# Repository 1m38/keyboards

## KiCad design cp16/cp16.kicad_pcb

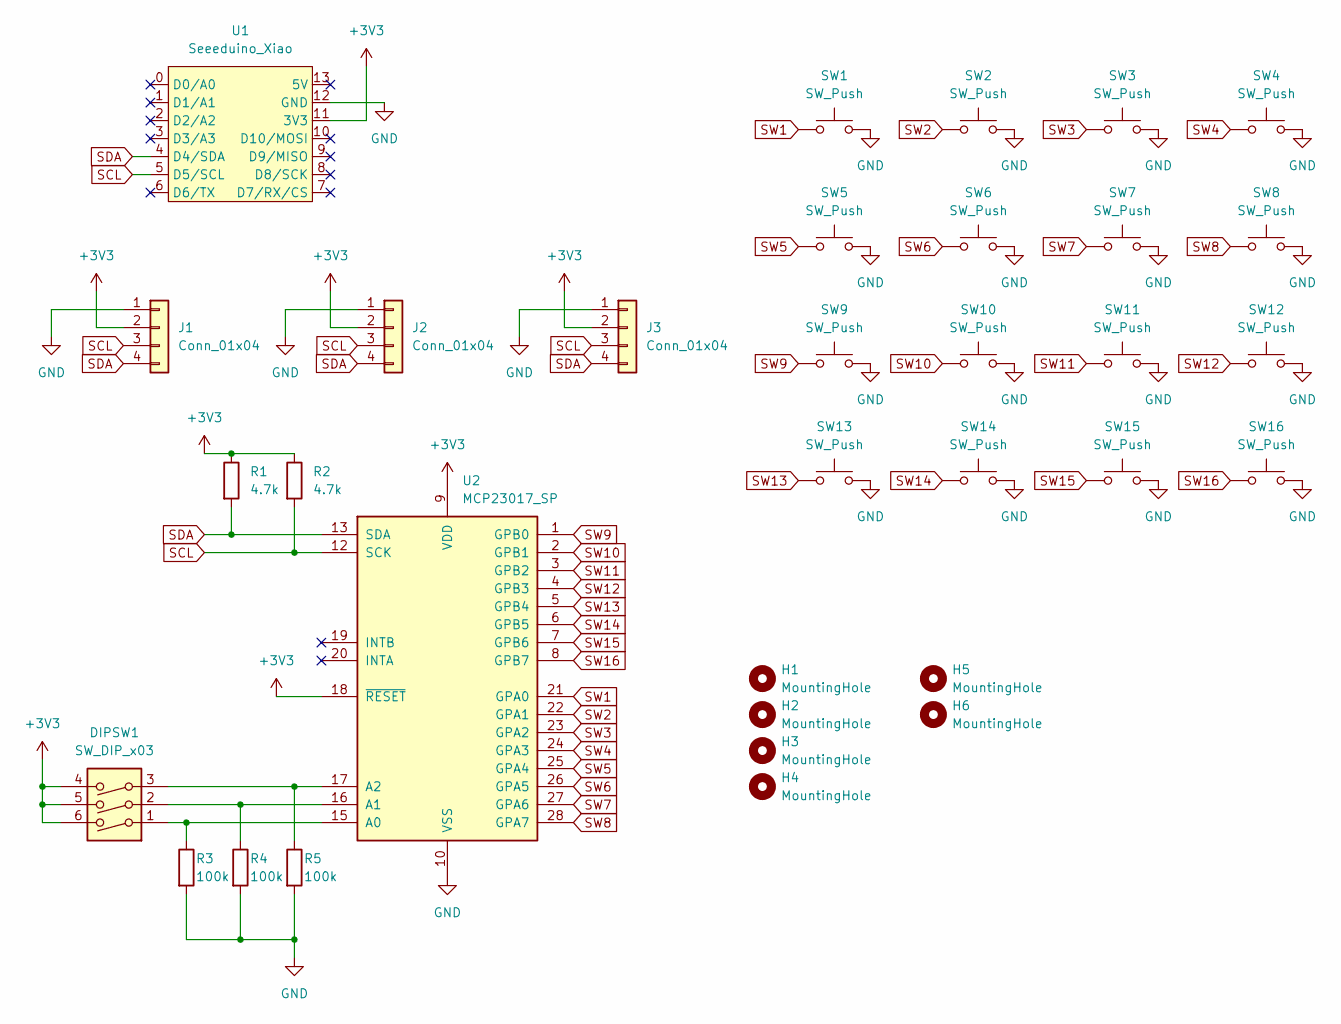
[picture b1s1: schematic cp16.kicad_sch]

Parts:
DIPSW1: SW_DIP_x03; DIP-6_W7.62mm
H1, H2, H3, H4: MountingHole; M2_HOLE_v2
H5, H6: MountingHole; M2_ScrewHole
J1, J2, J3: Conn_01x04; PinHeader_P2.54mm_I2C
R1, R2: 4.7k; R_Axial_DIN0207_L6.3mm_D2.5mm_P10.16mm_Horizontal
R3, R4, R5: 100k; R_Axial_DIN0207_L6.3mm_D2.5mm_P10.16mm_Horizontal
SW1, SW2, SW3, SW4, SW5, SW6, SW7, SW8, SW9, SW10, SW11, SW12, SW13, SW14, SW15, SW16: SW_Push; CherryMX_MidHeight_Choc_Hotswap_mod
U1: Seeeduino_Xiao; Seeed XIAO RP2040
U2: MCP23017_SP; DIP-28_W7.62mm

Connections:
+3V3: DIPSW1.4, DIPSW1.5, DIPSW1.6, J1.2, J2.2, J3.2, R1.1, R2.1, U1.11 (3V3), U2.9 (VDD), U2.18 (~RESET)
GND: J1.1, J2.1, J3.1, R3.2, R4.2, R5.2, SW1.2, SW2.2, SW3.2, SW4.2, SW5.2, SW6.2, SW7.2, SW8.2, SW9.2, SW10.2, SW11.2, SW12.2, SW13.2, SW14.2, SW15.2, SW16.2, U1.12 (GND), U2.10 (VSS)
unnamed: DIPSW1.1, R3.1, U2.15 (A0)
unnamed: DIPSW1.2, R4.1, U2.16 (A1)
unnamed: DIPSW1.3, R5.1, U2.17 (A2)
SCL: J1.3, J2.3, J3.3, R2.2, U1.5 (D5/SCL), U2.12 (SCK)
SDA: J1.4, J2.4, J3.4, R1.2, U1.4 (D4/SDA), U2.13 (SDA)
SW1: SW1.1, U2.21 (GPA0)
SW2: SW2.1, U2.22 (GPA1)
SW3: SW3.1, U2.23 (GPA2)
SW4: SW4.1, U2.24 (GPA3)
SW5: SW5.1, U2.25 (GPA4)
SW6: SW6.1, U2.26 (GPA5)
SW7: SW7.1, U2.27 (GPA6)
SW8: SW8.1, U2.28 (GPA7)
SW9: SW9.1, U2.1 (GPB0)
SW10: SW10.1, U2.2 (GPB1)
SW11: SW11.1, U2.3 (GPB2)
SW12: SW12.1, U2.4 (GPB3)
SW13: SW13.1, U2.5 (GPB4)
SW14: SW14.1, U2.6 (GPB5)
SW15: SW15.1, U2.7 (GPB6)
SW16: SW16.1, U2.8 (GPB7)

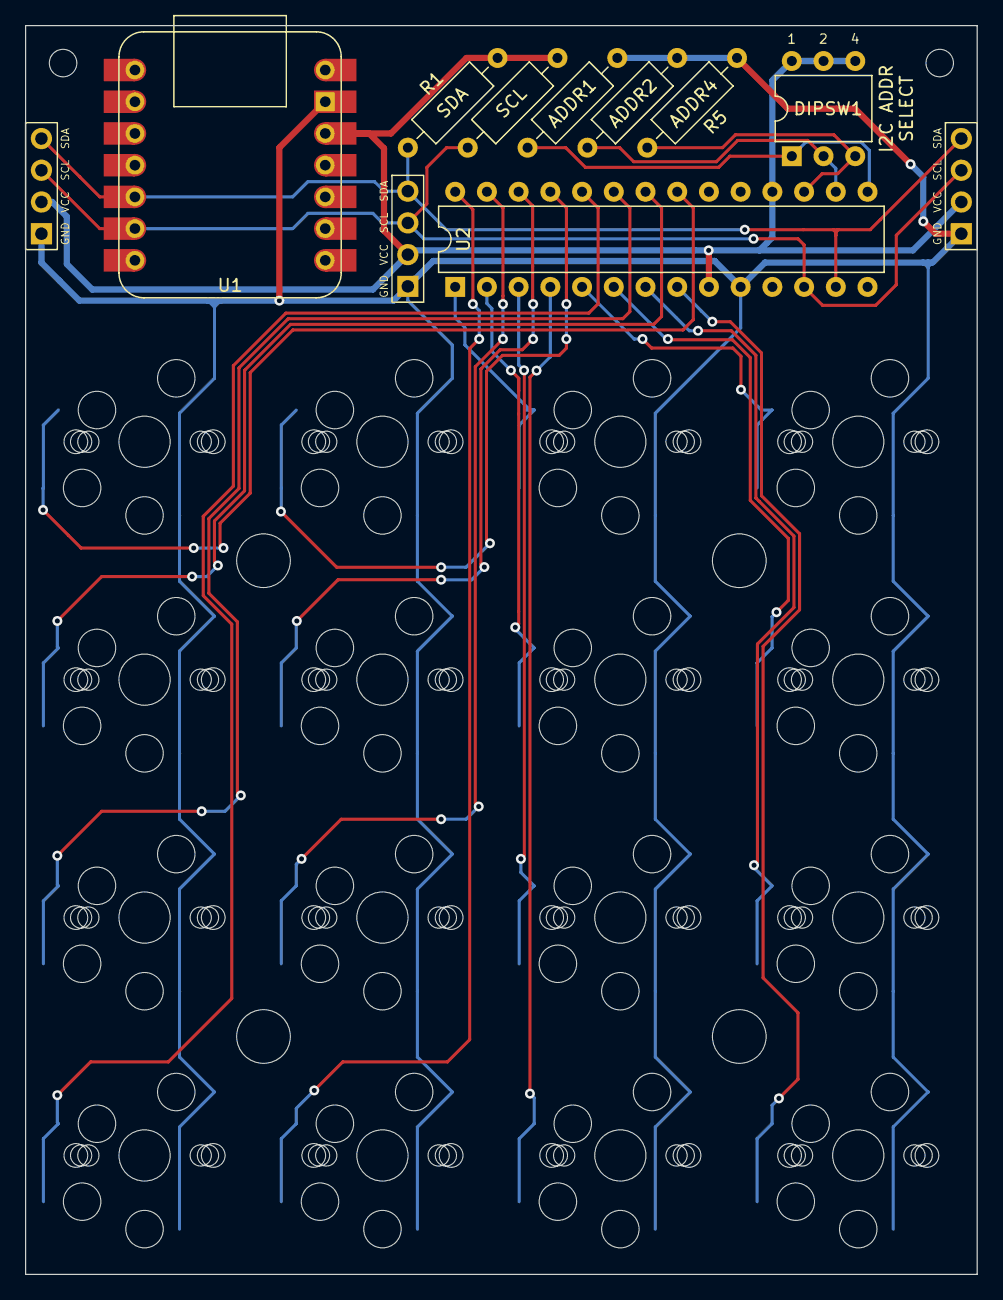
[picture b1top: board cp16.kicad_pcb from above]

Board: 2 copper layers, 76.2 x 100.0 mm, 33 parts (0 on the bottom side), 23 nets.

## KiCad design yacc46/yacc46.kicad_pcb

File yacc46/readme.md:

# yacc46

yacc46 is a 44-46keys self-made keyboard.

- [ビルドガイド(日本語)](./docs/buildguide_ja.md)
- [Full-scale drawing](./plate_v1.0/yacc46_fullscale_drawing.pdf)
- [Plate data(SVG)](./plate_v1.0)
- [Schematic](./schema.pdf)
- [KiCad PCB project](./yacc46.pro)
- [QMK Firmware](https://github.com/1m38/qmk_firmware/tree/1m38/yacc46/keyboards/yacc46)

## Notes

The yacc46 PCB project uses these libraries.

- [foostan/kbd](https://github.com/foostan/kbd)

The yacc46 logo uses the [JetBrains Mono](https://github.com/JetBrains/JetBrainsMono) font with some modifications.

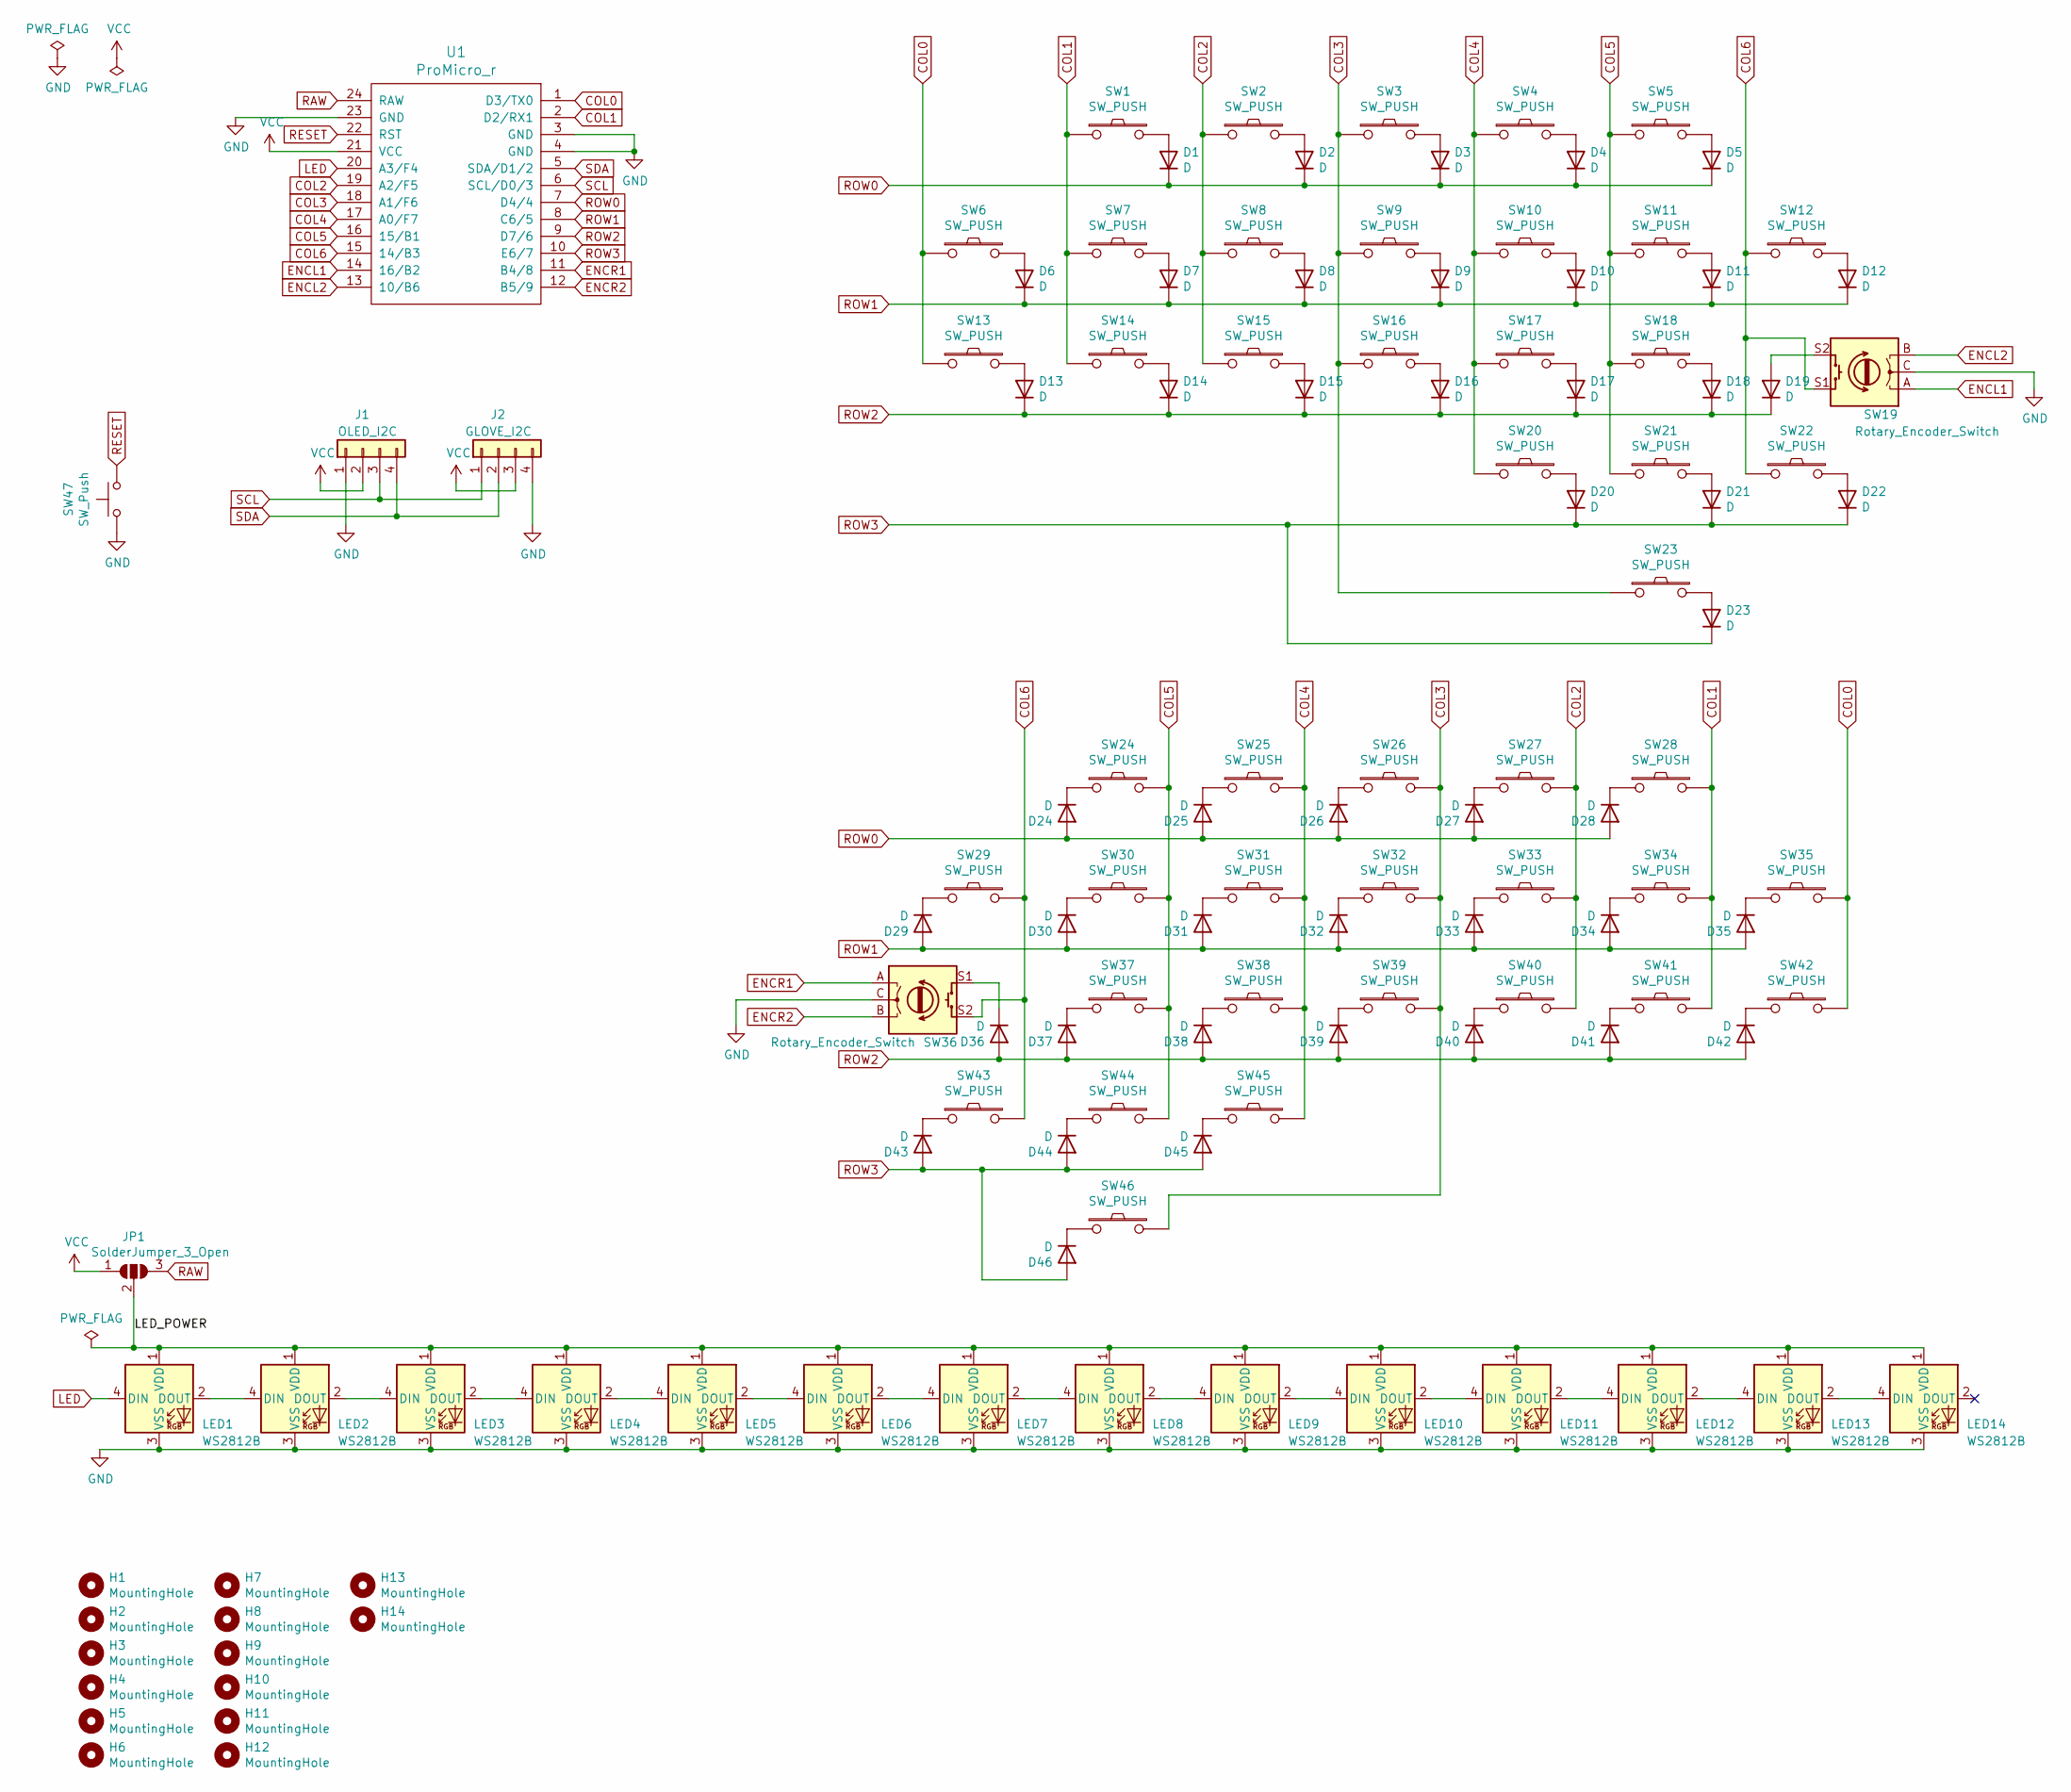
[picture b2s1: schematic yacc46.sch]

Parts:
D1, D2, D3, D4, D5, D6, D7, D8, D9, D10, D11, D12, D13, D14, D15, D16, D17, D18, D19, D20, D21, D22, D23, D24, D25, D26, D27, D28, D29, D30, D31, D32, D33, D34, D35, D36, D37, D38, D39, D40, D41, D42, D43, D44, D45, D46: D; D3_SMD_v2_silk
H1, H2, H3, H4, H5, H6, H7, H8, H9, H10, H11, H12: MountingHole; M2_HOLE_v2
H13, H14: MountingHole; MountingHole_2.2mm_M2
J1: OLED_I2C; OLED-0.96in
J2: GLOVE_I2C; Grove_I2C
JP1: SolderJumper_3_Open; SolderJumper-3_P2.0mm_Open_TrianglePad1.0x1.5mm
LED1, LED2, LED3, LED4, LED5, LED6, LED7, LED8, LED9, LED10, LED11, LED12, LED13, LED14: WS2812B; LED_WS2812B-PLCC4
SW1, SW2, SW3, SW4, SW5, SW6, SW7, SW8, SW9, SW10, SW11, SW12, SW13, SW14, SW15, SW16, SW17, SW18, SW20, SW21, SW22, SW23, SW24, SW25, SW26, SW27, SW28, SW29, SW30, SW31, SW32, SW33, SW34, SW35, SW37, SW38, SW39, SW40, SW41, SW42, SW43, SW44, SW45, SW46: SW_PUSH; CherryMX_Hotswap_mod
SW19, SW36: Rotary_Encoder_Switch; RotaryEncoder_Alps_EC11E-and-CherryMX-Hotswap
SW47: SW_Push; SW_PUSH_SMD_TVAF06-A020B-R_HandSolder
U1: ProMicro_r; ProMicro_v3

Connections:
/LED_POWER: JP1.2 (C), LED1.1 (VDD), LED2.1 (VDD), LED3.1 (VDD), LED4.1 (VDD), LED5.1 (VDD), LED6.1 (VDD), LED7.1 (VDD), LED8.1 (VDD), LED9.1 (VDD), LED10.1 (VDD), LED11.1 (VDD), LED12.1 (VDD), LED13.1 (VDD), LED14.1 (VDD)
COL0: SW6.1, SW13.1, SW35.2, SW42.2, U1.1 (D3/TX0)
COL1: SW1.1, SW7.1, SW14.1, SW28.2, SW34.2, SW41.2, U1.2 (D2/RX1)
COL2: SW2.1, SW8.1, SW15.1, SW27.2, SW33.2, SW40.2, U1.19 (A2/F5)
COL3: SW3.1, SW9.1, SW16.1, SW23.1, SW26.2, SW32.2, SW39.2, SW46.2, U1.18 (A1/F6)
COL4: SW4.1, SW10.1, SW17.1, SW20.1, SW25.2, SW31.2, SW38.2, SW45.2, U1.17 (A0/F7)
COL5: SW5.1, SW11.1, SW18.1, SW21.1, SW24.2, SW30.2, SW37.2, SW44.2, U1.16 (15/B1)
COL6: SW12.1, SW19.S1, SW22.1, SW29.2, SW36.S2, SW43.2, U1.15 (14/B3)
ENCL1: SW19.A, U1.14 (16/B2)
ENCL2: SW19.B, U1.13 (10/B6)
ENCR1: SW36.A, U1.11 (B4/8)
ENCR2: SW36.B, U1.12 (B5/9)
GND: J1.1, J2.4, LED1.3 (VSS), LED2.3 (VSS), LED3.3 (VSS), LED4.3 (VSS), LED5.3 (VSS), LED6.3 (VSS), LED7.3 (VSS), LED8.3 (VSS), LED9.3 (VSS), LED10.3 (VSS), LED11.3 (VSS), LED12.3 (VSS), LED13.3 (VSS), LED14.3 (VSS), SW19.C, SW36.C, SW47.1, U1.3 (GND), U1.4 (GND), U1.23 (GND)
LED: LED1.4 (DIN), U1.20 (A3/F4)
unnamed: D1.2 (A), SW1.2
unnamed: D2.2 (A), SW2.2
unnamed: D3.2 (A), SW3.2
unnamed: D4.2 (A), SW4.2
unnamed: D5.2 (A), SW5.2
unnamed: D6.2 (A), SW6.2
unnamed: D7.2 (A), SW7.2
unnamed: D8.2 (A), SW8.2
unnamed: D9.2 (A), SW9.2
unnamed: D10.2 (A), SW10.2
unnamed: D11.2 (A), SW11.2
unnamed: D12.2 (A), SW12.2
unnamed: D13.2 (A), SW13.2
unnamed: D14.2 (A), SW14.2
unnamed: D15.2 (A), SW15.2
unnamed: D16.2 (A), SW16.2
unnamed: D17.2 (A), SW17.2
unnamed: D18.2 (A), SW18.2
unnamed: D19.2 (A), SW19.S2
unnamed: D20.2 (A), SW20.2
unnamed: D21.2 (A), SW21.2
unnamed: D22.2 (A), SW22.2
unnamed: D23.2 (A), SW23.2
unnamed: D24.1 (K), SW24.1
unnamed: D25.1 (K), SW25.1
unnamed: D26.1 (K), SW26.1
unnamed: D27.1 (K), SW27.1
unnamed: D28.1 (K), SW28.1
unnamed: D29.1 (K), SW29.1
unnamed: D30.1 (K), SW30.1
unnamed: D31.1 (K), SW31.1
unnamed: D32.1 (K), SW32.1
unnamed: D33.1 (K), SW33.1
unnamed: D34.1 (K), SW34.1
unnamed: D35.1 (K), SW35.1
unnamed: D36.1 (K), SW36.S1
unnamed: D37.1 (K), SW37.1
unnamed: D38.1 (K), SW38.1
unnamed: D39.1 (K), SW39.1
unnamed: D40.1 (K), SW40.1
unnamed: D41.1 (K), SW41.1
unnamed: D42.1 (K), SW42.1
unnamed: D43.1 (K), SW43.1
unnamed: D44.1 (K), SW44.1
unnamed: D45.1 (K), SW45.1
unnamed: D46.1 (K), SW46.1
unnamed: LED1.2 (DOUT), LED2.4 (DIN)
unnamed: LED2.2 (DOUT), LED3.4 (DIN)
unnamed: LED3.2 (DOUT), LED4.4 (DIN)
unnamed: LED4.2 (DOUT), LED5.4 (DIN)
unnamed: LED5.2 (DOUT), LED6.4 (DIN)
unnamed: LED6.2 (DOUT), LED7.4 (DIN)
unnamed: LED7.2 (DOUT), LED8.4 (DIN)
unnamed: LED8.2 (DOUT), LED9.4 (DIN)
unnamed: LED10.2 (DOUT), LED11.4 (DIN)
unnamed: LED9.2 (DOUT), LED10.4 (DIN)
unnamed: LED11.2 (DOUT), LED12.4 (DIN)
unnamed: LED12.2 (DOUT), LED13.4 (DIN)
unnamed: LED13.2 (DOUT), LED14.4 (DIN)
RAW: JP1.3 (B), U1.24 (RAW)
RESET: SW47.2, U1.22 (RST)
ROW0: D1.1 (K), D2.1 (K), D3.1 (K), D4.1 (K), D5.1 (K), D24.2 (A), D25.2 (A), D26.2 (A), D27.2 (A), D28.2 (A), U1.7 (D4/4)
ROW1: D6.1 (K), D7.1 (K), D8.1 (K), D9.1 (K), D10.1 (K), D11.1 (K), D12.1 (K), D29.2 (A), D30.2 (A), D31.2 (A), D32.2 (A), D33.2 (A), D34.2 (A), D35.2 (A), U1.8 (C6/5)
ROW2: D13.1 (K), D14.1 (K), D15.1 (K), D16.1 (K), D17.1 (K), D18.1 (K), D19.1 (K), D36.2 (A), D37.2 (A), D38.2 (A), D39.2 (A), D40.2 (A), D41.2 (A), D42.2 (A), U1.9 (D7/6)
ROW3: D20.1 (K), D21.1 (K), D22.1 (K), D23.1 (K), D43.2 (A), D44.2 (A), D45.2 (A), D46.2 (A), U1.10 (E6/7)
SCL: J1.3, J2.1, U1.6 (SCL/D0/3)
SDA: J1.4, J2.2, U1.5 (SDA/D1/2)
VCC: J1.2, J2.3, JP1.1 (A), U1.21 (VCC)

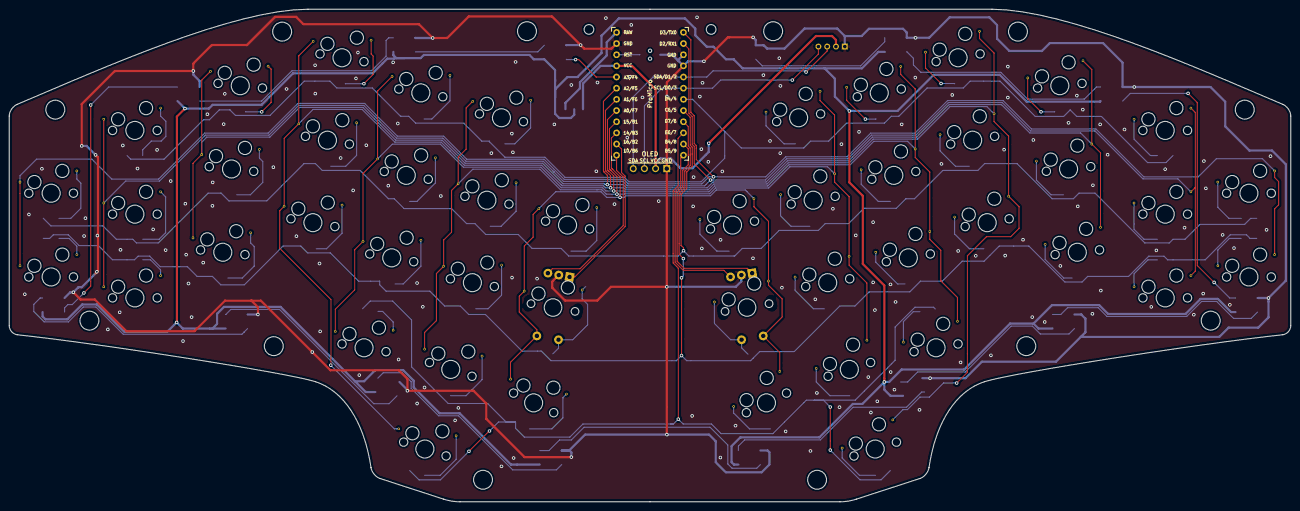
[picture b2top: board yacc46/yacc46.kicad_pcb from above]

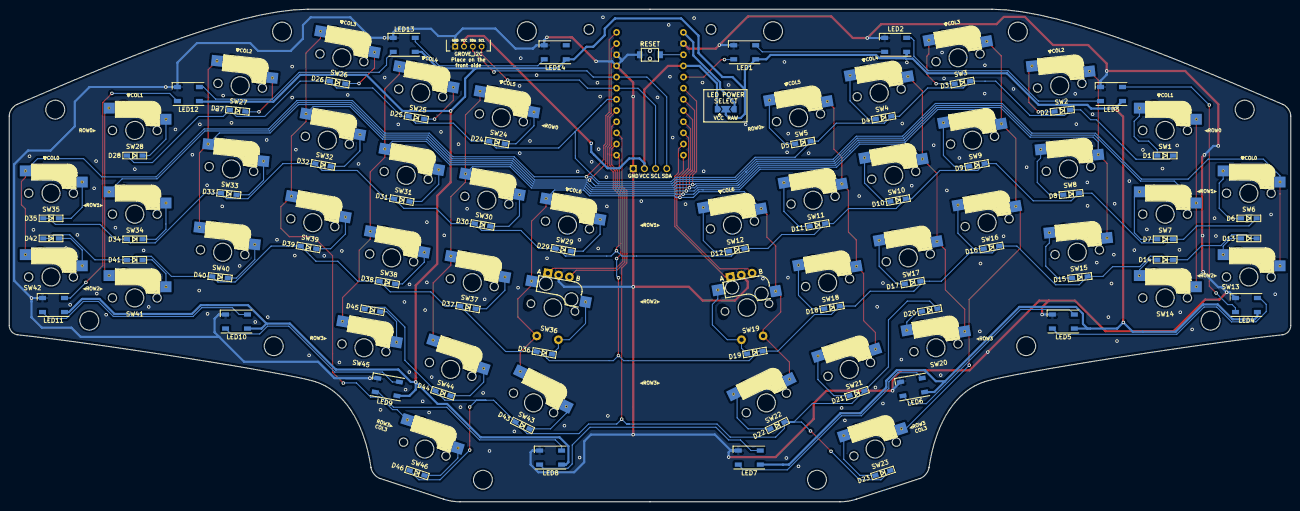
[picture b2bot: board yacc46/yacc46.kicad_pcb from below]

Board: 2 copper layers, 291.6 x 112.1 mm, 125 parts (62 on the bottom side), 82 nets.

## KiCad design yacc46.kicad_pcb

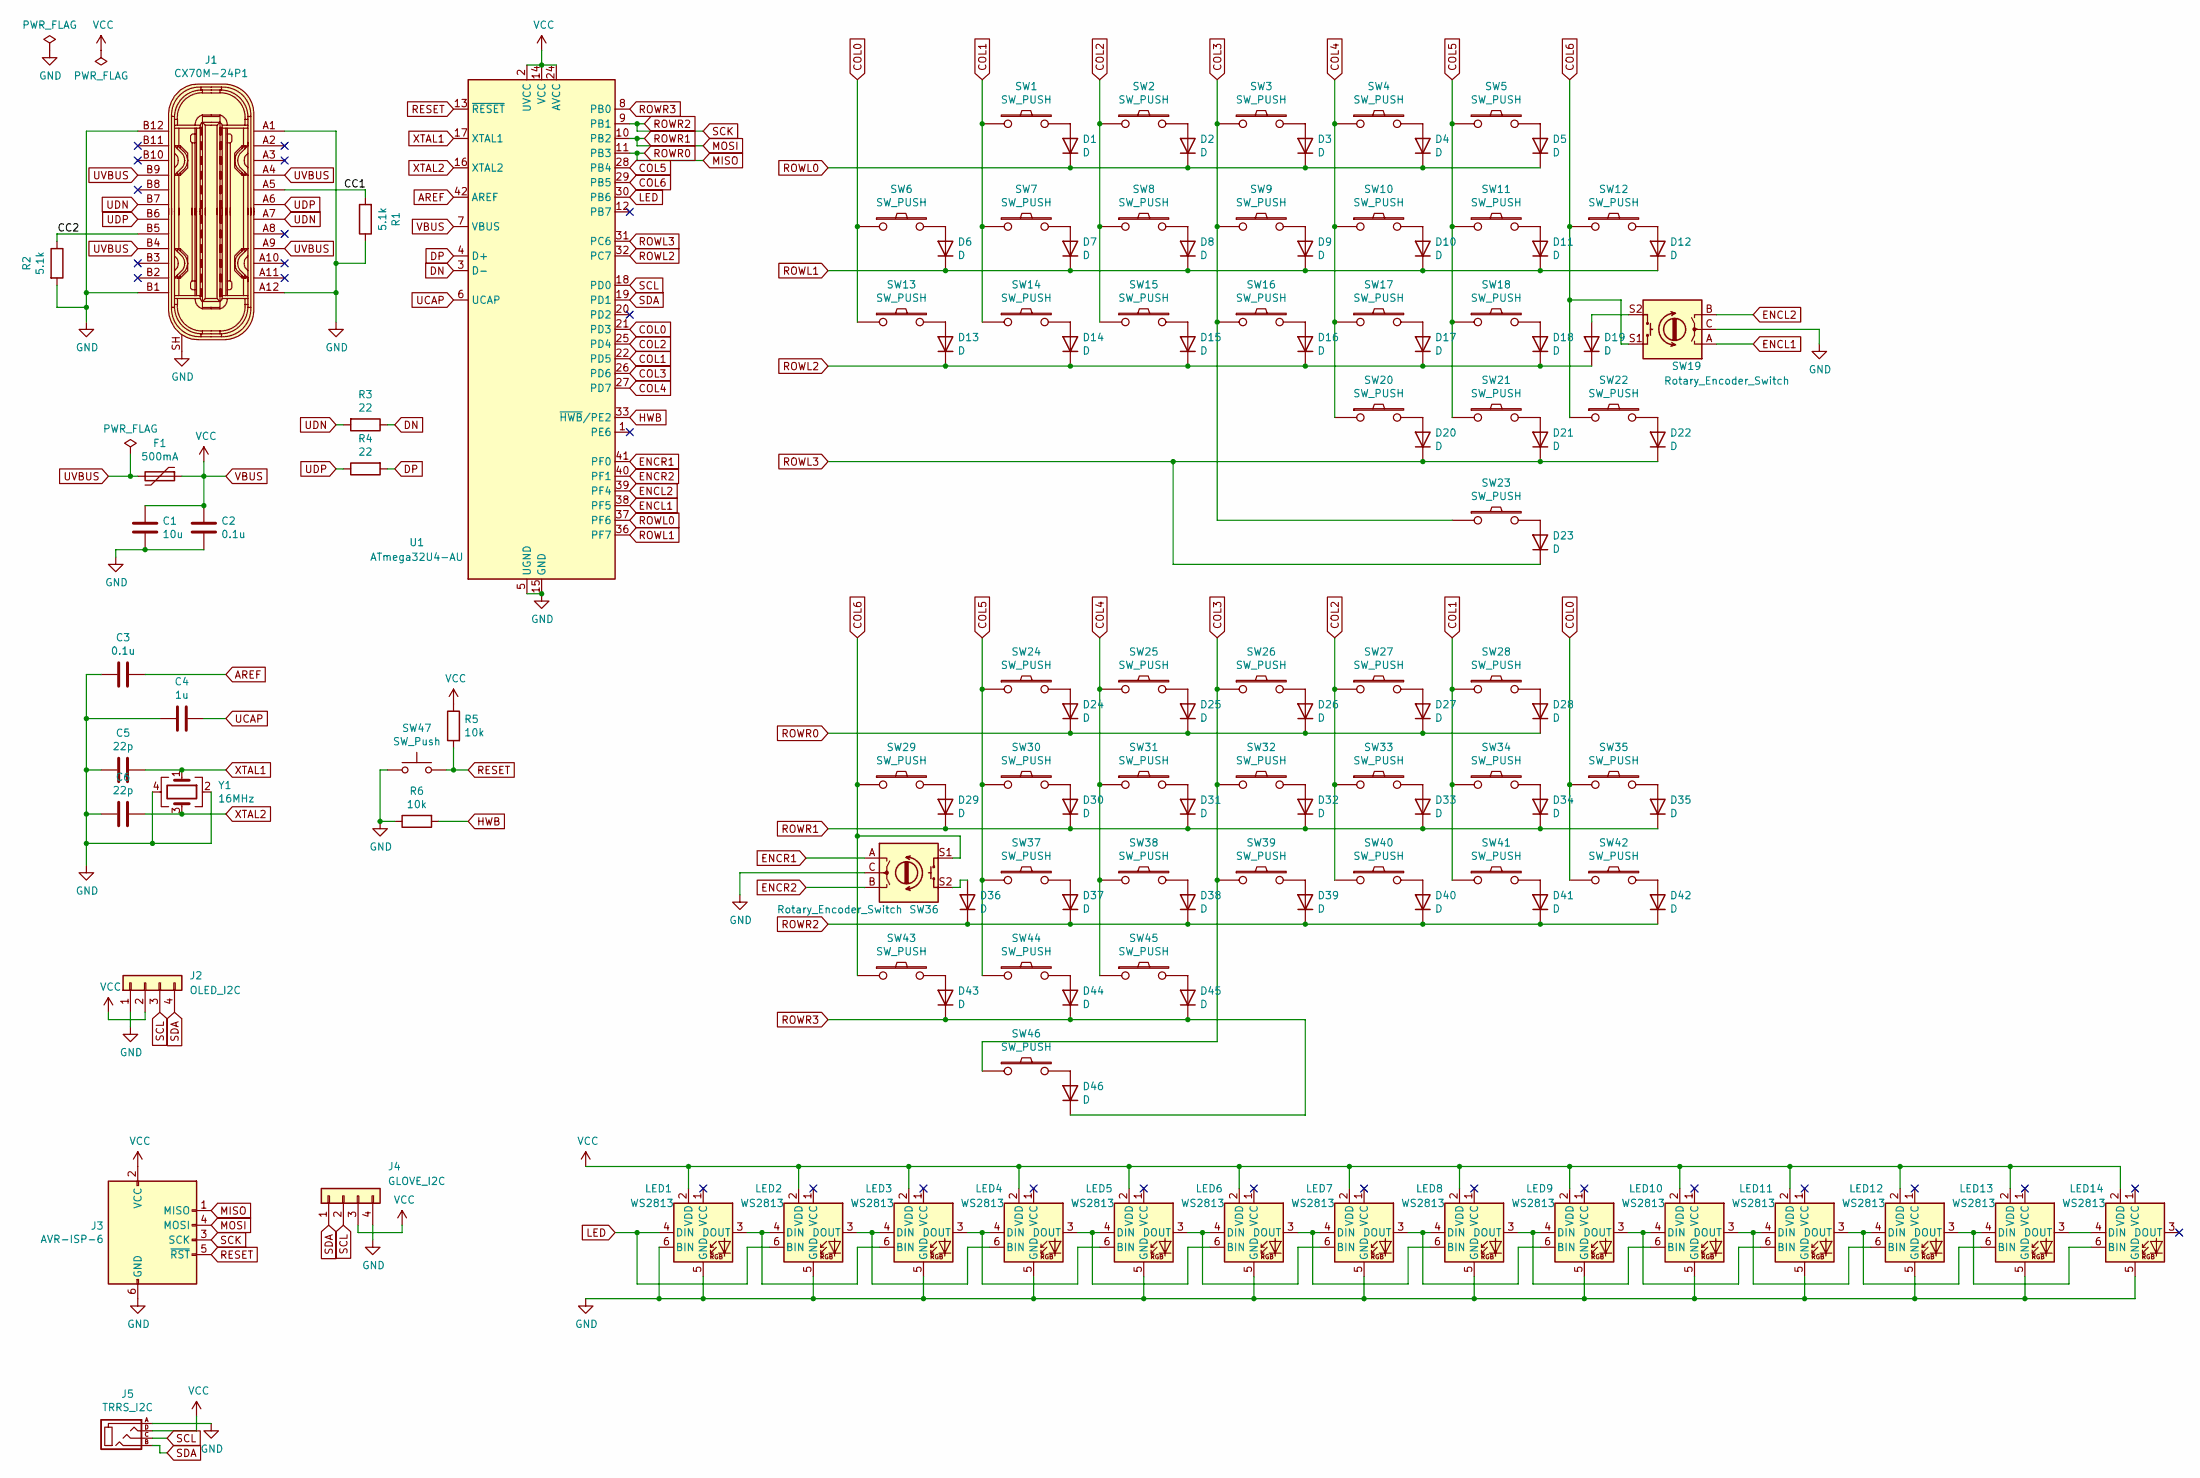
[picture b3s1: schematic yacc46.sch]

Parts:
C1: 10u; C_0805_2012Metric_Pad1.15x1.40mm_HandSolder
C2, C3: 0.1u; C_0805_2012Metric_Pad1.15x1.40mm_HandSolder
C4: 1u; C_0805_2012Metric_Pad1.15x1.40mm_HandSolder
C5, C6: 22p; C_0603_1608Metric_Pad1.05x0.95mm_HandSolder
D1, D2, D3, D4, D5, D6, D7, D8, D9, D10, D11, D12, D13, D14, D15, D16, D17, D18, D19, D20, D21, D22, D23, D24, D25, D26, D27, D28, D29, D30, D31, D32, D33, D34, D35, D36, D37, D38, D39, D40, D41, D42, D43, D44, D45, D46: D; D3_SMD_v2_silk
F1: 500mA; Bouns_PTC_ResettableFuse
J1: CX70M-24P1; USB-C_Female_CX70M-24P1; MPN CX70M-24P1; Digi-Key_PN H125292CT-ND
J2: OLED_I2C; OLED-0.96in
J3: AVR-ISP-6; ICSP-Header-ZigZag-Single
J4: GLOVE_I2C; Grove_I2C
J5: TRRS_I2C; MJ-4PP-9_1side_no-mask
LED1, LED2, LED3, LED4, LED5, LED6, LED7, LED8, LED9, LED10, LED11, LED12, LED13, LED14: WS2813; LED_WS2812_PLCC6_5.0x5.0mm_P1.6mm
R1, R2: 5.1k; R_0805_2012Metric_Pad1.15x1.40mm_HandSolder
R3, R4: 22; R_0805_2012Metric_Pad1.15x1.40mm_HandSolder
R5, R6: 10k; R_0805_2012Metric_Pad1.15x1.40mm_HandSolder
SW1, SW2, SW3, SW4, SW5, SW6, SW7, SW8, SW9, SW10, SW11, SW12, SW13, SW14, SW15, SW16, SW17, SW18, SW20, SW21, SW22, SW23, SW24, SW25, SW26, SW27, SW28, SW29, SW30, SW31, SW32, SW33, SW34, SW35, SW37, SW38, SW39, SW40, SW41, SW42, SW43, SW44, SW45, SW46: SW_PUSH; CherryMX_Hotswap_mod
SW19, SW36: Rotary_Encoder_Switch; RotaryEncoder_Alps_EC11E-and-CherryMX-Single
SW47: SW_Push; ResetSW_SKRPABE010
U1: ATmega32U4-AU; TQFP-44_10x10mm_P0.8mm
Y1: 16MHz; Crystal_SMD_2520-4Pin_2.5x2.0mm

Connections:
/CC1: J1.A5, R1.2
/CC2: J1.B5, R2.1
AREF: C3.1, U1.42 (AREF)
COL0: SW6.1, SW13.1, SW35.1, SW42.1, U1.21 (PD3)
COL1: SW1.1, SW7.1, SW14.1, SW28.1, SW34.1, SW41.1, U1.22 (PD5)
COL2: SW2.1, SW8.1, SW15.1, SW27.1, SW33.1, SW40.1, U1.25 (PD4)
COL3: SW3.1, SW9.1, SW16.1, SW23.1, SW26.1, SW32.1, SW39.1, SW46.1, U1.26 (PD6)
COL4: SW4.1, SW10.1, SW17.1, SW20.1, SW25.1, SW31.1, SW38.1, SW45.1, U1.27 (PD7)
COL5: SW5.1, SW11.1, SW18.1, SW21.1, SW24.1, SW30.1, SW37.1, SW44.1, U1.28 (PB4)
COL6: SW12.1, SW19.S1, SW22.1, SW29.1, SW36.S1, SW43.1, U1.29 (PB5)
DN: R3.1, U1.3 (D-)
DP: R4.2, U1.4 (D+)
ENCL1: SW19.A, U1.38 (PF5)
ENCL2: SW19.B, U1.39 (PF4)
ENCR1: SW36.A, U1.41 (PF0)
ENCR2: SW36.B, U1.40 (PF1)
GND: C1.1, C2.1, C3.2, C4.2, C5.2, C6.2, J1.A1, J1.A12, J1.B1, J1.B12, J1.SH, J2.1, J3.6 (GND), J4.4, J5.A, LED1.5 (GND), LED1.6 (BIN), LED2.5 (GND), LED3.5 (GND), LED4.5 (GND), LED5.5 (GND), LED6.5 (GND), LED7.5 (GND), LED8.5 (GND), LED9.5 (GND), LED10.5 (GND), LED11.5 (GND), LED12.5 (GND), LED13.5 (GND), LED14.5 (GND), R1.1, R2.2, R6.1, SW19.C, SW36.C, SW47.1, U1.5 (UGND), U1.15 (GND), U1.23 (GND), U1.35 (GND), U1.43 (GND), Y1.2, Y1.4
HWB: R6.2, U1.33 (~HWB~/PE2)
LED: LED1.4 (DIN), LED2.6 (BIN), U1.30 (PB6)
MISO: D24.1 (K), D25.1 (K), D26.1 (K), D27.1 (K), D28.1 (K), J3.1 (MISO), U1.11 (PB3)
MOSI: D29.1 (K), D30.1 (K), D31.1 (K), D32.1 (K), D33.1 (K), D34.1 (K), D35.1 (K), J3.4 (MOSI), U1.10 (PB2)
unnamed: D1.2 (A), SW1.2
unnamed: D2.2 (A), SW2.2
unnamed: D3.2 (A), SW3.2
unnamed: D4.2 (A), SW4.2
unnamed: D5.2 (A), SW5.2
unnamed: D6.2 (A), SW6.2
unnamed: D7.2 (A), SW7.2
unnamed: D8.2 (A), SW8.2
unnamed: D9.2 (A), SW9.2
unnamed: D10.2 (A), SW10.2
unnamed: D11.2 (A), SW11.2
unnamed: D12.2 (A), SW12.2
unnamed: D13.2 (A), SW13.2
unnamed: D14.2 (A), SW14.2
unnamed: D15.2 (A), SW15.2
unnamed: D16.2 (A), SW16.2
unnamed: D17.2 (A), SW17.2
unnamed: D18.2 (A), SW18.2
unnamed: D19.2 (A), SW19.S2
unnamed: D20.2 (A), SW20.2
unnamed: D21.2 (A), SW21.2
unnamed: D22.2 (A), SW22.2
unnamed: D23.2 (A), SW23.2
unnamed: D24.2 (A), SW24.2
unnamed: D25.2 (A), SW25.2
unnamed: D26.2 (A), SW26.2
unnamed: D27.2 (A), SW27.2
unnamed: D28.2 (A), SW28.2
unnamed: D29.2 (A), SW29.2
unnamed: D30.2 (A), SW30.2
unnamed: D31.2 (A), SW31.2
unnamed: D32.2 (A), SW32.2
unnamed: D33.2 (A), SW33.2
unnamed: D34.2 (A), SW34.2
unnamed: D35.2 (A), SW35.2
unnamed: D36.2 (A), SW36.S2
unnamed: D37.2 (A), SW37.2
unnamed: D38.2 (A), SW38.2
unnamed: D39.2 (A), SW39.2
unnamed: D40.2 (A), SW40.2
unnamed: D41.2 (A), SW41.2
unnamed: D42.2 (A), SW42.2
unnamed: D43.2 (A), SW43.2
unnamed: D44.2 (A), SW44.2
unnamed: D45.2 (A), SW45.2
unnamed: D46.2 (A), SW46.2
unnamed: LED1.3 (DOUT), LED2.4 (DIN), LED3.6 (BIN)
unnamed: LED2.3 (DOUT), LED3.4 (DIN), LED4.6 (BIN)
unnamed: LED3.3 (DOUT), LED4.4 (DIN), LED5.6 (BIN)
unnamed: LED4.3 (DOUT), LED5.4 (DIN), LED6.6 (BIN)
unnamed: LED5.3 (DOUT), LED6.4 (DIN), LED7.6 (BIN)
unnamed: LED6.3 (DOUT), LED7.4 (DIN), LED8.6 (BIN)
unnamed: LED7.3 (DOUT), LED8.4 (DIN), LED9.6 (BIN)
unnamed: LED10.3 (DOUT), LED11.4 (DIN), LED12.6 (BIN)
unnamed: LED9.3 (DOUT), LED10.4 (DIN), LED11.6 (BIN)
unnamed: LED8.3 (DOUT), LED9.4 (DIN), LED10.6 (BIN)
unnamed: LED11.3 (DOUT), LED12.4 (DIN), LED13.6 (BIN)
unnamed: LED12.3 (DOUT), LED13.4 (DIN), LED14.6 (BIN)
unnamed: LED13.3 (DOUT), LED14.4 (DIN)
RESET: J3.5 (~RST), R5.2, SW47.2, U1.13 (~RESET)
ROWL0: D1.1 (K), D2.1 (K), D3.1 (K), D4.1 (K), D5.1 (K), U1.37 (PF6)
ROWL1: D6.1 (K), D7.1 (K), D8.1 (K), D9.1 (K), D10.1 (K), D11.1 (K), D12.1 (K), U1.36 (PF7)
ROWL2: D13.1 (K), D14.1 (K), D15.1 (K), D16.1 (K), D17.1 (K), D18.1 (K), D19.1 (K), U1.32 (PC7)
ROWL3: D20.1 (K), D21.1 (K), D22.1 (K), D23.1 (K), U1.31 (PC6)
ROWR2: D36.1 (K), D37.1 (K), D38.1 (K), D39.1 (K), D40.1 (K), D41.1 (K), D42.1 (K), J3.3 (SCK), U1.9 (PB1)
ROWR3: D43.1 (K), D44.1 (K), D45.1 (K), D46.1 (K), U1.8 (PB0)
SCL: J2.3, J4.2, J5.C, U1.18 (PD0)
SDA: J2.4, J4.1, J5.B, U1.19 (PD1)
UCAP: C4.1, U1.6 (UCAP)
UDN: J1.A7, J1.B7, R3.2
UDP: J1.A6, J1.B6, R4.1
UVBUS: F1.2, J1.A4, J1.A9, J1.B4, J1.B9
VBUS: C1.2, C2.2, F1.1, J2.2, J3.2 (VCC), J4.3, J5.D, LED1.2 (VDD), LED2.2 (VDD), LED3.2 (VDD), LED4.2 (VDD), LED5.2 (VDD), LED6.2 (VDD), LED7.2 (VDD), LED8.2 (VDD), LED9.2 (VDD), LED10.2 (VDD), LED11.2 (VDD), LED12.2 (VDD), LED13.2 (VDD), LED14.2 (VDD), R5.1, U1.2 (UVCC), U1.7 (VBUS), U1.14 (VCC), U1.24 (AVCC), U1.34 (VCC), U1.44 (AVCC)
XTAL1: C5.1, U1.17 (XTAL1), Y1.1
XTAL2: C6.1, U1.16 (XTAL2), Y1.3

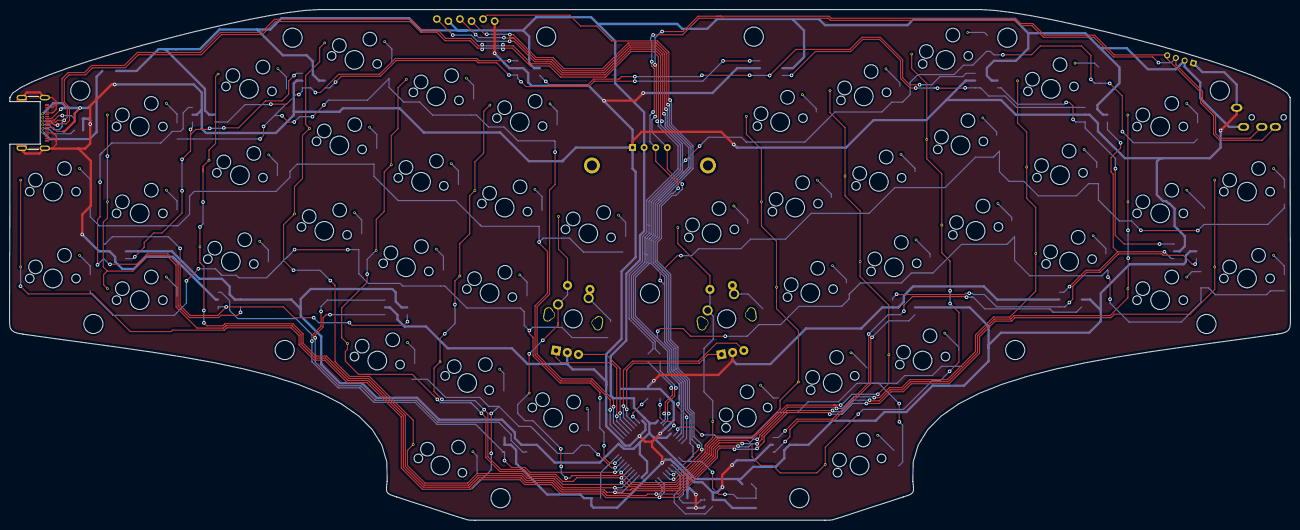
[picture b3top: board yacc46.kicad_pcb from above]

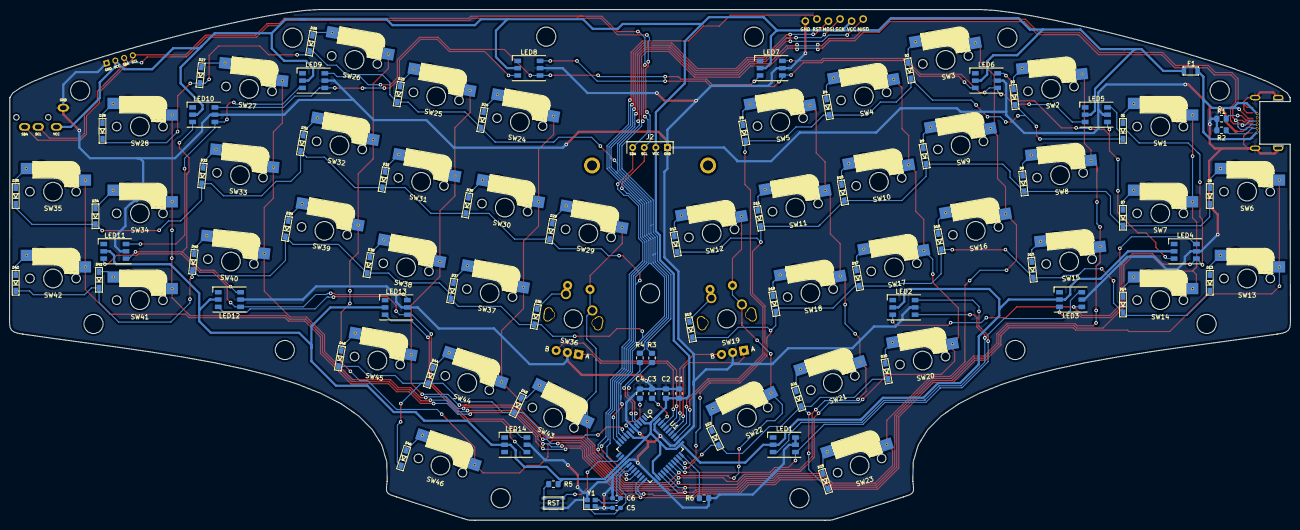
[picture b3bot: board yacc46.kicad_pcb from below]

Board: 2 copper layers, 281.1 x 112.1 mm, 142 parts (77 on the bottom side), 96 nets.

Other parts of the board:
HOLE1, HOLE2, HOLE3, HOLE4, HOLE5, HOLE6, HOLE7, HOLE8, HOLE9, HOLE10, HOLE11, HOLE12, HOLE13#2: Val**; M2_HOLE_v2
HOLE13, HOLE14: MountingHole_2.2mm_M2
